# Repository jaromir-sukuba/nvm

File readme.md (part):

***Please note this nanovoltmeter design was superseded by a new and better design, which will go public in [this Github repository](https://github.com/jaromir-sukuba/nvm2). Soon(TM)***

## What is in this repository?
Here is the complete set of design files, manufacturing data, source files, test results and other resources that I used in the process of building a nanovoltmeter. This process was not a coincidence, but a response to the nanovoltmeter challenge by TiN on [his website](https://xdevs.com/article/nvm_comp/)

## What is a nanovoltmeter and what is it good for?
Well, a nanovoltmeter is a voltmeter that has the sensitivity, noise and stability to resolve voltages down to the nanovolt. While many multimeters do have quite sensitive low voltage ranges, the resolution (least significant digit) is usually in the order of hundreds of nanovolts - and value of this last digit is often diminished by the noise and nonlinearity of the meter. So, for proper low signal measurements, having a higher sensitivity is mandatory.
Measurement of such low voltages is useful for many applications, for example resolving small voltage differences in various differential and bridge circuits and the measurement of very small resistances - with an appropriate current source.
Commercial nanovoltmeters do exist, like the Keithley model 2182A or Keysight 34420A, but with a hefty price tag, so a DIY design definitely has its place.

## xDevs challenge
While I have been tinkering with DIY test and measurement tools for a while now, I never had an impulse to discover the nanovolt world. Such a trigger happened on September 2nd, 2021, when TiN from xdevs site launched the [nanovolt challenge](https://xdevs.com/article/nvm_comp/). In nutshell, it called for the design of an open-source nanovoltmeter, with parameters comparable to commercial designs and a timeframe of 256 days. That is a non-trivial task, and in my case it was even more so, because I had not only never designed low signal circuits before, but had I never operated a nanovoltmeter. That is quite an unfavorable starting position and jumping into the deep end rather than dipping my toes into the problematics. To ease my mind, I waited a few days to see how others reacted on the [eevblog forum](https://www.eevblog.com/forum/metrology/nanovolt-design-challenge-build-and-show-your-own-nv-meter-in-256-days/?all). I can't say that it encouraged me.
On the other hand, I spent a few days researching online sources and studying the service manuals of proven test gear from reputable vendors. Too bad they stopped supplying us with schematics in early 90s of the last century; but even that material was very helpful in understanding both what the requirements are for such a meter, as well as the means to achieve it.

## NVM design, part 1 - design requirements
Armed with new knowledge I started dissecting the challenge requirements. 

> Have local onboard power regulation. Single common DC (+9 to +24 VDC) or 110/220VAC mains input jack is expected.

Okay, I think I can do this. On the other hand, any reasonable mains-powered voltmeter has to have an isolated PSU section which powers the input dividers/amplifiers and ADC, so that the measurement potential could be unrelated to the digital section with all the user and communication IO - which is needed to be earthed or somewhere close to that potential.
This one calls for either DC or AC power, but it could be combined by having a PSU operating from an appropriate DC voltage (12V sounds like a good starting point) and attach a small AC/DC SMPS to provide power from mains.

> Provide DC Voltage measurement ranges ±100 µV or below and include ±1V and ±10VDC range.

This one looks innocent, but having both 10V and 100uV input on the same jacks implies either switching input amplifiers, or inserting a voltage divider into the signal path, preferably through a relay. Some older nanovoltmeters (Keithley model 181) had two different inputs - one for higher ranges, another one with low TEMF connector for sensitive ranges.

> Have at least two user-accessible input channels for signal to be measured.

Oh my, another relay. Relays are good, but may introduce offset errors into signals due to thermal voltages (TEMF, short for Thermal Electromotive Force) generated on the contacts, when the relay heats up from coil power. The voltages may be around a few microvolts down to nanovolts, definitely something to consider in this design. TEMF is the main enemy of the nanovoltmeter and this acronym will be used in following text a few more times.

> Have low-thermal connection interface to minimize thermal EMF parasitic errors.

TEMF again, I told you so.   
  
> Provide at least 5½-digit resolution for each reading.

Sounds reasonable. I've done long-scale ADC projects like [voltmeter](https://www.eevblog.com/forum/metrology/diy-6-5-digit-voltmeter/) and [voltohmmeter](https://www.eevblog.com/forum/metrology/diy-6-digit-handheld-volohmmeter/msg2978912/#msg2978912) so perhaps I could recycle something and also bring something new to the table. I think commercial sigma-delta A-to-D converters would do the job too, but a DIY ADC definitely has more to it.

> Ability to digitize input DC signal with resolution at least 10 nV and noise better than 30 nV peak to peak over at least 0.1-10 Hz bandwidth.

More numeric requirements, nice. 30nVp-p in 10Hz bandwidth is not a very relaxed requirement - older meters like Keithley model 181 would not cut it, current models so-so.

> Have autozero functionality to correct for static offsets.

That is a logical requirement. I will put in some more effort by introducing autocalibration.

> Have galvanic isolated analog front end, with isolation resistance to earth/chassis better than 10 GΩ.

That is what I proposed earlier, too. 

> Device should have ADC (any type) integrated.

This is likely to frame the project into standalone modus operandi.

> Have good long-term stability and use ovenized DC voltage reference (LM399, LTZ1000 or LTFLU with oven).

I wouldn't think of using anything worse than an LM399 (or ADR1399) anyway.

> Provide RJ45 Ethernet and/or IEEE-488 GPIB interface for communications with external world / external equipment.

Fair point. USB is simpler, though.

> 40W total input power budget (friendly to battery operation for sensitive experiments)

You wouldn't want your nanovoltmeter to consume more than 40W anyway. 40W is quite a bit of heat and it's not easy to dissipate it without introducing more TEMF errors.

> Device should be fully operational as standalone device (e.g. no debuggers or external equipment attached to make it work).

OK, fair.

After a bit of optimization, I came up with this block diagram.

It's basically done to fit the requirements above, with a few spicy parts I added for extra fun.
Input from either input connection is selected via an input multiplexor. There is also a third input, to be discussed later. This MUX passes the selected channel to a low noise amplifier (LNA) to be amplified and then routed via another MUX into the main amplifier. whose output is brought to the ADC. This ADC has a nominal 10V input range, so that the basic range with LNA is 10mV (10mV x 1000 = 10V). In order to have even more sensitive ranges, the main amplifier has option to switch to x1 (pass-through), x10 and x100 gain, combined into additional 1mV and 100uV ranges. When the LNA is bypassed, the input signal is brought directly to the main amplifier, allowing for 10V, 1V and 100mV ranges, seamlessly covering 100uV to 10V input range. That would make a nanovoltmeter already, but I added two more blocks - first is easy, a low-pass filter (also known as LPF) to cut down noise, especially on sensitive ranges. Another one is an auto-calibration block, which serves to decide the gain of both amplifiers. Ideally, the meter needs only to know its onboard 7V reference voltage and can derive lower ranges automatically without calibration/adjustment and keep it precise after resistors in dividers and amplifier drift due to age or temperature.
The entire upper portion of the circuit is held behind an isolation barrier in order to keep the input terminals separated from the power supply potential - either external DC or mains voltage. The bottom section consists mainly of the PSU and digital circuitry, including user IO and communication channels, like Ethernet and USB. For the added fun factor I also included GPIB as a low priority subproject.

## NVM design, part 2 - divide and conquer

Designing such an instrument, especially on a DIY base, is a lot of pingponging between mechanical and eletrical design. I could imagine how large the thing would be (say, an A4 page size as a footprint) and I knew I had to cram everything inside. Choosing a larger enclosure would give me much more freedom and other benefits (like easier dissipation of device heat, helping fight TEMF), but would be impractically large. Finding an appropriate enclosure wasn't easy - at first I thought of using G756 I used before in my [DIY SMU](https://github.com/jaromir-sukuba/J-SMU), but I preferred metal enclosures here - because of shielding from electrical interference, and with a steel enclosure even a bit of shielding from magnetic interference. Metal also helps with heat dissipation. Finally I settled on the 1EP802825 from Modushop.
That was the right time to take a look at the electrical domain. The Earthy and floating parts (separated by an isolation barrier) have to be physically separated in sub-enclosures (that calls for two PCBs minimum) and in order to have easier debugging and modification of the circuit, I decided to separate the floating part into two PCBs. One would hold FPGA control, the reference and ADC, while another one would consist of both amplifiers and ACAL circuits. Since the enclosure is 80mm tall, there is no problem stacking at least two PCBs on top of each other, via pin headers and metric spacers.
So, two PCBs for the floating part, one for the earthy part. The backside connectors have to be mounted somehow - here I added another PCB. The front panel pushbuttons also needed a PCB for mechanical reasons, that resulted in a total count of 5 PCBs. I named the PCBs with human names and gave them functionality:

**Bart** - I felt like this one will be tricky and there will be problems. Contains LNA, main amplifier, ACAL dividers and MUXes.  
**Homer** - largest PCB, contains FPGA, ADC, references. Closely related to Bart.  
**Lisa** - communication board, back panel PCB  
**Meggie** - simplest PCB, just to hold buttons  
**Marge** - contains PSU to feed all other PCBs, plus digital circuits.  

With the electronics roughly separated into basic blocks, I returned to mechanical design. By the time I finished first sketches of the schematics files, I received the enclosure, so I could start with more practical details. It's much easier to visualize potential problems having the real enclosure in hand compared to studying 3D files (if any, right). For circuit separation I opted for two sheet metal sub-enclosures.
. The smaller portion on right holding analog circuitry, the left portion holding earthy circuits - it's somehow shorter, to make room for a backpanel PCB.
I designed a bunch of holes into the enclosures to allow mounting PCBs via metric spacers, and now having physical constraints, I jumped back to PCB design.

## NVM design, part 3 - selected details of circuit operation
In this section I'll discuss a few selected design choices of this instrument.
#### LNA (Bart board)
I went through a few design iterations of the LNA and it took me roughly half of the development time. I tried DC-coupled JFET amplifiers, AC coupled JFET amplifiers in chopper configuration for DC operation as well as paralleling opamps. The parallel configuration brought me the least amount of headache and despite the insane amount of components used, it is not that expensive after all. As best in class, IF3602 JFETs are both expensive and suffer by huge parameter spread, making them quite an expensive solution. There are cheaper JFETs around, but their noise parameters mean more paralleled pieces - with problems they bring, for example binning and matching. More transistors or fewer low noise types also bring more gate capacitance, requiring more circuit support to diminish its influence. Enclosing the amplifier into chopper configuration brings more issues to solve - for example I had to deal with input current and temperature gradients increasing voltage offset. It's very likely that all those problems are solvable with more time and effort and would make an LNA with lower noise and drift than what I have in the current NVM, but at some point I decided to go a different way and built the LNA out of massively parallel off-the-shelf opamp amplifier. Integrated autozero/chopper opamps do have much better temperature stability and input current, so after a bit of searching and comparing I opted for MCP6V51 from Microchip, as the one with very good price/performance ratio. Typical input noise voltage is specified at 210nV in 10Hz bandwidth and I confirmed this experimentally by building a 35 piece opamp board first. 

The noise parameters were in good agreement with the datasheet values, that gave me confidence to go this way. As calculated, I need at least 50 MCP6V51s to get under 30nV p-p criteria, so I opted for 100 pieces, in 10x10 matrix, as per the schematic below

Each of the first stage gain blocks (with 10 amplifiers in parallel noninverting configuration) is brought to a second stage summing amplifier, and all 10 of the second stage amplifiers are summed into a third, and final, amplifier, with an overall gain of 1000.
The last stage summing amplifier is also used to inject a voltage to null the offset voltage of LNA. The Bart board has a DAC and its amplifiers (U119 and U120) for this reason. The DAC's second channel is designed to compensate for input current - by injecting a current of opposite sign into the LNA input. I measured the uncompensated current to be around 2nA and in my current hardware the injection resistor isn't fitted on the board. By using this feature, I expect a current well below 100pA.
The LNA injects ground current into the ground net of the circuit, and the current is dependent on input voltage (and therefore output voltage, too). Ground current may cause unwanted voltage shifts between ground potentials of the circuit, especially at high gains. To counteract this ground current, amplifier with U121 is set up to source current of opposite polarity into the ground, into areas where the LNA resides.
The Bart board is 4-layer, with internal layers being ground nets, for both electrical and thermal reasons.

#### ADC (Homer board)
The ADC is of the integrating, charge balancing type with residual integrator voltage reading. SN74LV4053 is used for integrator current steering, the integrator is of the classic two opamp composite type. The FPGA does multiple jobs here, apart from orchestrating actions around the ADC, it also provides an interface between isolated serial link and multiple digital outputs used to switch relays, multiplexer and analog filter and does startup timing for smooth PSU startup.
I measured INL of ADC against a Solartron 7081 as reference. A 0-10V voltage sweep was provided by a DIY precision voltage source (LTZ1000A reference, AD5791B DAC). Measured INL graph:

The INL of this magnitude may not be obviously needed for this application, but I wanted to employ ACAL functionality, where voltage transfer between ranges expects good INL of the ADC, so I was after good linearity and spent some time honing it.

#### PSU (Marge board)
My first idea for the PSU was to use two back-to-back 50Hz transformers. One would provide a few volts (providing first isolation barrier and ground reference) and the second would step it up to the level appropriate for +-16V and 5V DC outputs. Later I expended this idea by using an audio frequency amplifier circuit to feed the second transformer and omitting the first transformer. Using an AF amplifier (fed by an appropriate oscillator) to drive the transformer has a few advantages - the whole circuit could be powered from a single DC voltage and the oscillation frequency can be adjusted to find a good compromise between leakage and efficiency. Using classic linear amplifiers would bring way too much thermal dissipation into the enclosure, so I opted for the cheap and plentiful TPS3116 D-class amplifier. The oscillator signal - either from a local single opamp multivibrator or amplified signal provided by the MCU - is shaped by a series of lowpass filters, so that the amplifier is fed by a low harmonic content signal. Transformer secondary is brought to a fairly standard set of regulators - LM317/337 and 7805.
I measured ground leakage from the isolated PSU section and its efficiency as function of driving frequency.

As per expectations, a lower frequency also brings lower leakage current, but going too low causes efficiency to plummet at some point. I opted for 48Hz, where I measured leakage well below 200nA p-p. At this level, leakage measurement is very sensitive to nearby electric fields and conducted interference. After enclosing the test setup in a shielded box, the measured leakage fell to 40nA p-p, indicating the previous measurement was too pessimistic. I believe even the 40nA figure is pessimistic still and influenced by the shielding setup and the oscilloscope I used. For proper test results I'd need a larger shielded cage and a battery powered oscilloscope, but I didn't want to go that far.
The PSU design brought interesting detail to the game. In case of overload, TPS3116 will turn off the load drive. That sounds innocent, but may be problemtic in this case - because after powerup the reference is cold, so the heater takes a significant amount of current during powerup. To add insult to injury, all decoupling/bulk capacitors are discharged, even more increasing the powerup current spike. The spike causes TPS3116 to shut down for a moment, then it tries to restart the load, ending up in the same large spike, repeating again and again.
To mitigate this issue, two fixes were made:
 - PSU driving starts from higher frequency, slowly (over course of a few seconds) it descends to the final 48Hz value. Voltage on the isolated secondary ramps up much slower, allowing circuits to power up smoothly.  
 - Voltage reference heating current (large current spike when left untreated) and LNA power supply voltage is held off until 10 seconds after FPGA power gets stable, at which point heater current is enbled, and LNA power turns on two seconds later.

## Mechanical parts
While the enclosure is centered around the Modushop enclosure, a few more mechanical parts were needed.

#### Reference cover
This two-part 3D printed component prevents airflows around ADR1399 reference, decreasing its noise somehow.

#### Lisa board holder
This 3D printed component keeps Lisa board in its place on back panel.

#### LNA cover
This 3D printed component provides insulation of LNA board area from airflows.

The amount of influence on the readings was suprising to me. Here are two graphs of the shorted input measurement, one with cover, one without, the RMS noise voltage is nearly twofold for naked LNA.

#### Side PCB
The original modushop enclosure fitted the outer enclosure panel by screwing to side metal sheets by self tapping screws. I didn't like this, so I drilled the original holes for self-tappers into 3,5mm diameter and mounted dedicated mechanical PCB with nothing but holes and copper plane to solder M3 nuts. This PCB keeps the internal chassis and outer shields in single piece. I think this part would be somehow better made out of >3mm thick aluminium of the same size, with drilled and tapped holes, but PCB seems to work fine for now.

#### Push button rod
This is three piece 3D printed component to extend main switch shaft to front panel.  
TODO pictures.

#### Front panel construction
Display cover is epoxied into the front panel cutout, display is bolted to Meggie board and this board is bolted the to font panel.
TODO picture of perspex cutout

#### Internal construction details

Complete internal construction without top cover

Dump of construction photographs is in imgur gallery [here](https://imgur.com/a/fnK1Evj)

## NVM usage
#### Local interface

13 keys are provided for instrument operation, plus 2-line by 20 characters vacuum fluorescent display.
After startup the meter enters default (measurement) mode, with settings read from EEPROM. Typical display layout:

The first line displays measured voltage and range in obvious way.  
Second line in this example indicates following states:  
CH1 - selected channel 1. Could be either 1 or 2.  
Z0 - zero function (see below) is not active on this range. Could be either 0 or 1.  
10NPLC - ADC integration time in powerline cycle multiplies. Could be either 1, 2, 5, 10 or 20.  
ETH1 - Ethernet is connected and IP address provided via DHCP. Could be either 0 or 1.  

Buttons functions:  
**INPUT** - by clicking this button, the instrument toggles between Input 1 and Input 2 on the 4-pin LEMO connector.  
**ZERO** - this function enables zeroing measured value (by subtracting constant voltage offset measured at the instant of enabling the function). Each range has its offset value and is independent of other ranges. Zeroing for given range is disabled by second button press.  
**FILT** - pressing this button displays analog filter, digital filter and NPLC settings. Each hit of the button moves focus to next setting (value is changed by pressing UP/DOWN controls), third hit returns to default measurement display.  
**ACAL** - pressing this button starts ACAL procedure and saves the calibration constants into EEPROM memory.  
**TRIG** - not used in this firmware revision.  
**STORE** - not used in this firmware revision.  
**RECALL** - not used in this firmware revision.  
**MENU** - enables menu. Moving across menu items is done by pressing UP and DOWN keys. Enter enables editing the item value - editing is performed using UP and DOWN keys. Escaping from the menu is possible via ESC button, saving and escaping via MENU button.  
**AUTO** - not used in this firmware revision.  
**ENTER** - apart from function in menu function, pressing ENTER in default mode displays IP address of the instrument (if attached to ethernet). Pressing ENTER again returns back to default state.  
**UP/DOWN** - in menu or filter editing it serves function described above, in default mode it selects higher or lower measurement range.  

#### Remote interface
Instrument could be controlled remotely via ethernet interface, by issuing SCPI-compatible commands.  
\*IDN? - returns instrument identification  
\*RST - resets instrument  
\*CLS - clear status  
SYSTem:ERRor[:NEXT] - lists system error  
SYSTem:ERRor:COUNt? - return amount of system errors  
SYSTem:VERSion? - returns instrument version string  
MEASure:VOLTage? - returns value of measured voltage  
CALibration:VREF - single float parameter, sets value of 7V reference voltage (the only input for ACAL procedure)  
CALibration:VREF? - returns value of 7V reference voltage  
CALibration:UNLock - single integer parameter, locks (0) or unlocks (1) access to calibration EEPROM  
CALibration:SAVe - if access to calibration EEPROM is unlocked, this command saves actual calibration into EEPROM  
CALibration:ACAL - starts ACAL procedure  
SENSe:CHANnel - single integer parameter, sets channel 1 or 2  
SENSe:CHANnel? - returns actual channel number  
SENSe:RANGe - single integer parameter, sets range 1 (100uV) to 6 (10V)  
SENSe:RANGe? - returns actual range number  
SENSe:DFILter - single integer parameter, sets digital filter to 1, 2, 4, 8, 16, 32 or 64 samples  
SENSe:DFILter? - returns digital filter setting  
SENSe:AFILter - single integer parameter, sets analog filter off (0) or on (1)  
SENSe:AFILter? - returns analog filter setting  
SENSe:DIGits - single integer parameter, sets nubmer of displayed digits - 3 to 6  
SENSe:DIGits? - returns nubmer of displayed digits  
SENSe:NPLC - single integer parameter, sets ADC integration period in NPLC cycles to 1NPLC (0), or 2NPLC (1), or 5NPLC (2), or 10NPLC (3), or 20NPLC (4)  
SENSe:NPLC? - returns ADC integration period  
SENSe:AZero - single integer parameter, sets ADC autozero off (0) or on (1)  
SENSe:AZero? - return ADC autozero setting  
SYSTem:BEEPer - single integer parameter, sets beeper off (0) or on (1)  
SYSTem:BEEPer? - return beeper state  

NVM is fully calibrated by ACAL feature. For this it needs to have its reference voltage setup in calibration memory before running ACAL function. The value is accessible only through remote interface and its CALibration:VREF command. If the reference value in calibration memory is outside 6,95-7,3V range, default value 7,05V is assumed. At the moment, individual range calibration isn't supported, but probably will be in future firmware revisions.

## NVM project goals
In this section I'll discuss the performance of this instrument and project goals. 
#### Noise
The main criteria of this project was to achieve low noise at the lowest voltage range. In order to assess this, I logged 20 seconds of shorted input measurements at 100uV range, with no autozero, 2NPLC (integration time 40ms) and 10Hz analog filter on.

The noise is below 25nV p-p.
#### Stability
I recorded roughly 9 hours worth of data with shorted input, while logging ambient temperature too. Meter set to 10NPLC, autozero on, analog filter on. I separated the data into 64 seconds long chunks, averaged it and used as data points. I tried to control the room temperature to obtain some variation.

There is no clear temperature dependency. I read the data as sensitivity to temperature changes is perhaps more prominent than the tempco of the instrument.
#### Linearity
I measured the same INL of the NVM against Keithley 2010 as reference meter.

I believe it lies within acceptable margin for 6,5 digit meter.
#### Bandwidth and normal mode rejection
I measured ADC transfer function for sine input with 1Vp-p amplitude, stepped from 1Hz to 80Hz. Meter was set to 2NPLC, no autozero, analog filter on, 10V range.

Resulting bandwidth for -3dB is between 9 and 10Hz, normal mode rejection for 25, 50 and 75Hz is around -90dB
#### Stepping the input with various voltages from Keithley 260 voltage source
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
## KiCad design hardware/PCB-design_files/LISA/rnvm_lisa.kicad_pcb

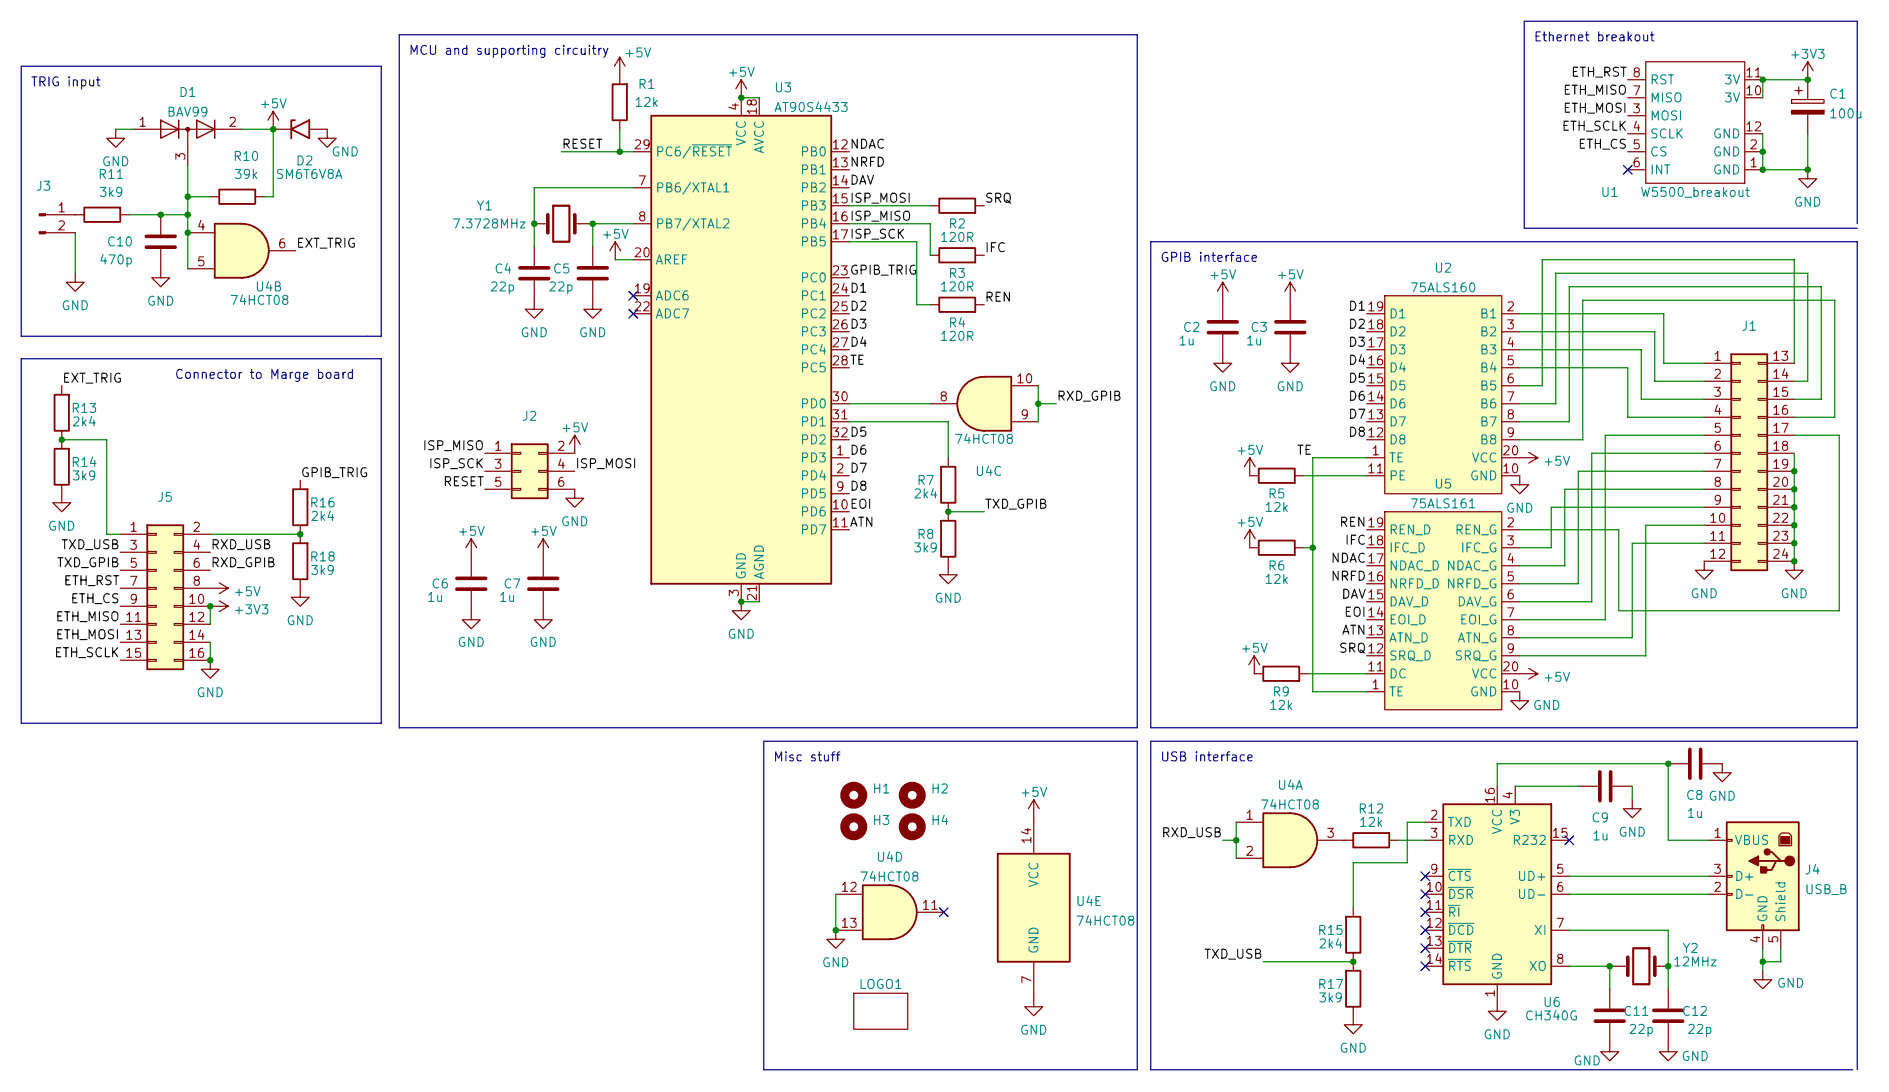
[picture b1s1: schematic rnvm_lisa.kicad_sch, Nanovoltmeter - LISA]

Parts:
C1: 100u; CP_EIA-7132-28_AVX-C_Pad2.72x3.50mm_HandSolder
C2, C3, C6, C7, C8, C9: 1u; C_0805_2012Metric_Pad1.18x1.45mm_HandSolder
C4, C5, C11, C12: 22p; C_0805_2012Metric_Pad1.18x1.45mm_HandSolder
C10: 470p; C_0805_2012Metric_Pad1.18x1.45mm_HandSolder
D1: BAV99; SOT-23
D2: SM6T6V8A; D_SMB
H1, H2, H3, H4: MountingHole; MountingHole_3.2mm_M3_DIN965_Pad
J1: Centronics 24, socket; CENTR_24P_F
J2: IDC_6pin; IDC-Header_2x03_P2.54mm_Vertical
J3: Conn_01x02_Male; Molex_KK-254_AE-6410-02A_1x02_P2.54mm_Vertical
J4: USB_B; USB_B_Lumberg_2411_02_Horizontal
J5: IDC_16; IDC-Header_2x08_P2.54mm_Vertical
LOGO1: PCB logo; logo_rpg7x9
R1, R5, R6, R9, R12: 12k; R_MiniMELF_MMA-0204
R2, R3, R4: 120R; R_MiniMELF_MMA-0204
R7, R13, R15, R16: 2k4; R_MiniMELF_MMA-0204
R8, R11, R14, R17, R18: 3k9; R_MiniMELF_MMA-0204
R10: 39k; R_MiniMELF_MMA-0204
U1: W5500_breakout; W5500_bo
U2: 75ALS160; SOIC-20W_7.5x12.8mm_P1.27mm
U3: AT90S4433; TQFP-32_7x7mm_P0.8mm
U4: 74HCT08; TSSOP-14_4.4x5mm_P0.65mm
U5: 75ALS161; SOIC-20W_7.5x12.8mm_P1.27mm
U6: CH340G; SOIC-16_3.9x9.9mm_P1.27mm
Y1: 7.3728MHz; Crystal_SMD_HC49-SD
Y2: 12MHz; Crystal_SMD_HC49-SD

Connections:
+3V3: C1.1, J5.10, J5.12, U1.10 (3V), U1.11 (3V)
+5V: C2.2, C3.2, C6.2, C7.2, D1.2 (A), D2.1 (A1), J2.2, J5.8, R1.2, R5.1, R6.1, R9.1, R10.2, U2.20 (VCC), U3.4 (VCC), U3.6 (VCC), U3.18 (AVCC), U3.20 (AREF), U4.14 (VCC), U5.20 (VCC)
/ATN: U3.11 (PD7), U5.13 (ATN_D)
/D1: U2.19 (D1), U3.24 (PC1)
/D2: U2.18 (D2), U3.25 (PC2)
/D3: U2.17 (D3), U3.26 (PC3)
/D4: U2.16 (D4), U3.27 (PC4)
/D5: U2.15 (D5), U3.32 (PD2)
/D6: U2.14 (D6), U3.1 (PD3)
/D7: U2.13 (D7), U3.2 (PD4)
/D8: U2.12 (D8), U3.9 (PD5)
/DAV: U3.14 (PB2), U5.15 (DAV_D)
/EOI: U3.10 (PD6), U5.14 (EOI_D)
/ETH_CS: J5.9, U1.5 (CS)
/ETH_MISO: J5.11, U1.7 (MISO)
/ETH_MOSI: J5.13, U1.3 (MOSI)
/ETH_RST: J5.7, U1.8 (RST)
/ETH_SCLK: J5.15, U1.4 (SCLK)
/EXT_TRIG: R13.2, U4.6
/GPIB_TRIG: R16.2, U3.23 (PC0)
/IFC: R3.2, U5.18 (IFC_D)
/ISP_MISO: J2.1, R3.1, U3.16 (PB4)
/ISP_MOSI: J2.4, R2.1, U3.15 (PB3)
/ISP_SCK: J2.3, R4.1, U3.17 (PB5)
/NDAC: U3.12 (PB0), U5.17 (NDAC_D)
/NRFD: U3.13 (PB1), U5.16 (NRFD_D)
/REN: R4.2, U5.19 (REN_D)
/RESET: J2.5, R1.1, U3.29 (PC6/~RESET)
/RXD_GPIB: J5.6, U4.9, U4.10
/RXD_USB: J5.4, U4.1, U4.2
/SRQ: R2.2, U5.12 (SRQ_D)
/TE: R6.2, U2.1 (TE), U3.28 (PC5), U5.1 (TE)
/TXD_GPIB: J5.5, R7.1, R8.2
/TXD_USB: J5.3, R15.1, R17.2
GND: C1.2, C2.1, C3.1, C4.2, C5.2, C6.1, C7.1, C8.2, C9.2, C10.2, C11.2, C12.2, D1.1 (K), D2.2 (A2), J1.12, J1.18, J1.19, J1.20, J1.21, J1.22, J1.23, J1.24, J2.6, J3.2, J4.4 (GND), J4.5 (Shield), J5.14, J5.16, R8.1, R14.1, R17.1, R18.1, U1.1 (GND), U1.2 (GND), U1.12 (GND), U2.10 (GND), U3.3 (GND), U3.5 (GND), U3.21 (AGND), U4.7 (GND), U4.12, U4.13, U5.10 (GND), U6.1 (GND)
unnamed: C4.1, U3.7 (PB6/XTAL1), Y1.1
unnamed: C5.1, U3.8 (PB7/XTAL2), Y1.2
unnamed: C8.1, J4.1 (VBUS), U6.16 (VCC)
unnamed: C9.1, U6.4 (V3)
unnamed: C10.1, D1.3 (K), R10.1, R11.2, U4.4, U4.5
unnamed: C11.1, U6.8 (XO), Y2.2
unnamed: C12.1, U6.7 (XI), Y2.1
unnamed: J1.1, U2.2 (B1)
unnamed: J1.2, U2.3 (B2)
unnamed: J1.3, U2.4 (B3)
unnamed: J1.4, U2.5 (B4)
unnamed: J1.5, U5.7 (EOI_G)
unnamed: J1.6, U5.6 (DAV_G)
unnamed: J1.7, U5.5 (NRFD_G)
unnamed: J1.8, U5.4 (NDAC_G)
unnamed: J1.9, U5.3 (IFC_G)
unnamed: J1.10, U5.9 (SRQ_G)
unnamed: J1.11, U5.8 (ATN_G)
unnamed: J1.13, U2.6 (B5)
unnamed: J1.14, U2.7 (B6)
unnamed: J1.15, U2.8 (B7)
unnamed: J1.16, U2.9 (B8)
unnamed: J1.17, U5.2 (REN_G)
unnamed: J3.1, R11.1
unnamed: J4.2 (D-), U6.6 (UD-)
unnamed: J4.3 (D+), U6.5 (UD+)
unnamed: J5.1, R13.1, R14.2
unnamed: J5.2, R16.1, R18.2
unnamed: R5.2, U2.11 (PE)
unnamed: R7.2, U3.31 (PD1)
unnamed: R9.2, U5.11 (DC)
unnamed: R12.1, U4.3
unnamed: R12.2, U6.3 (RXD)
unnamed: R15.2, U6.2 (TXD)
unnamed: U3.30 (PD0), U4.8

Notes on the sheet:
MCU and supporting circuitry
Connector to Marge board
Misc stuff
USB interface
TRIG input
Ethernet breakout
GPIB interface

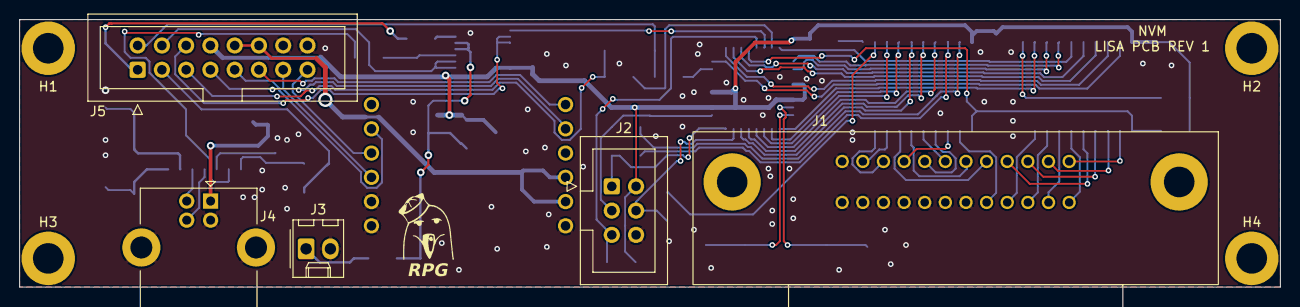
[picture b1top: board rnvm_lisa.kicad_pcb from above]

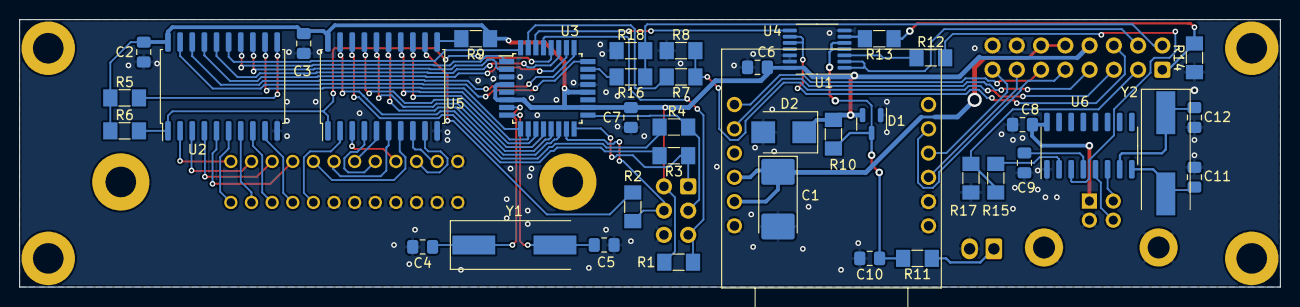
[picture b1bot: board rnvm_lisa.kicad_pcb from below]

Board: 2 copper layers, 132.0 x 28.0 mm, 50 parts (40 on the bottom side), 70 nets.

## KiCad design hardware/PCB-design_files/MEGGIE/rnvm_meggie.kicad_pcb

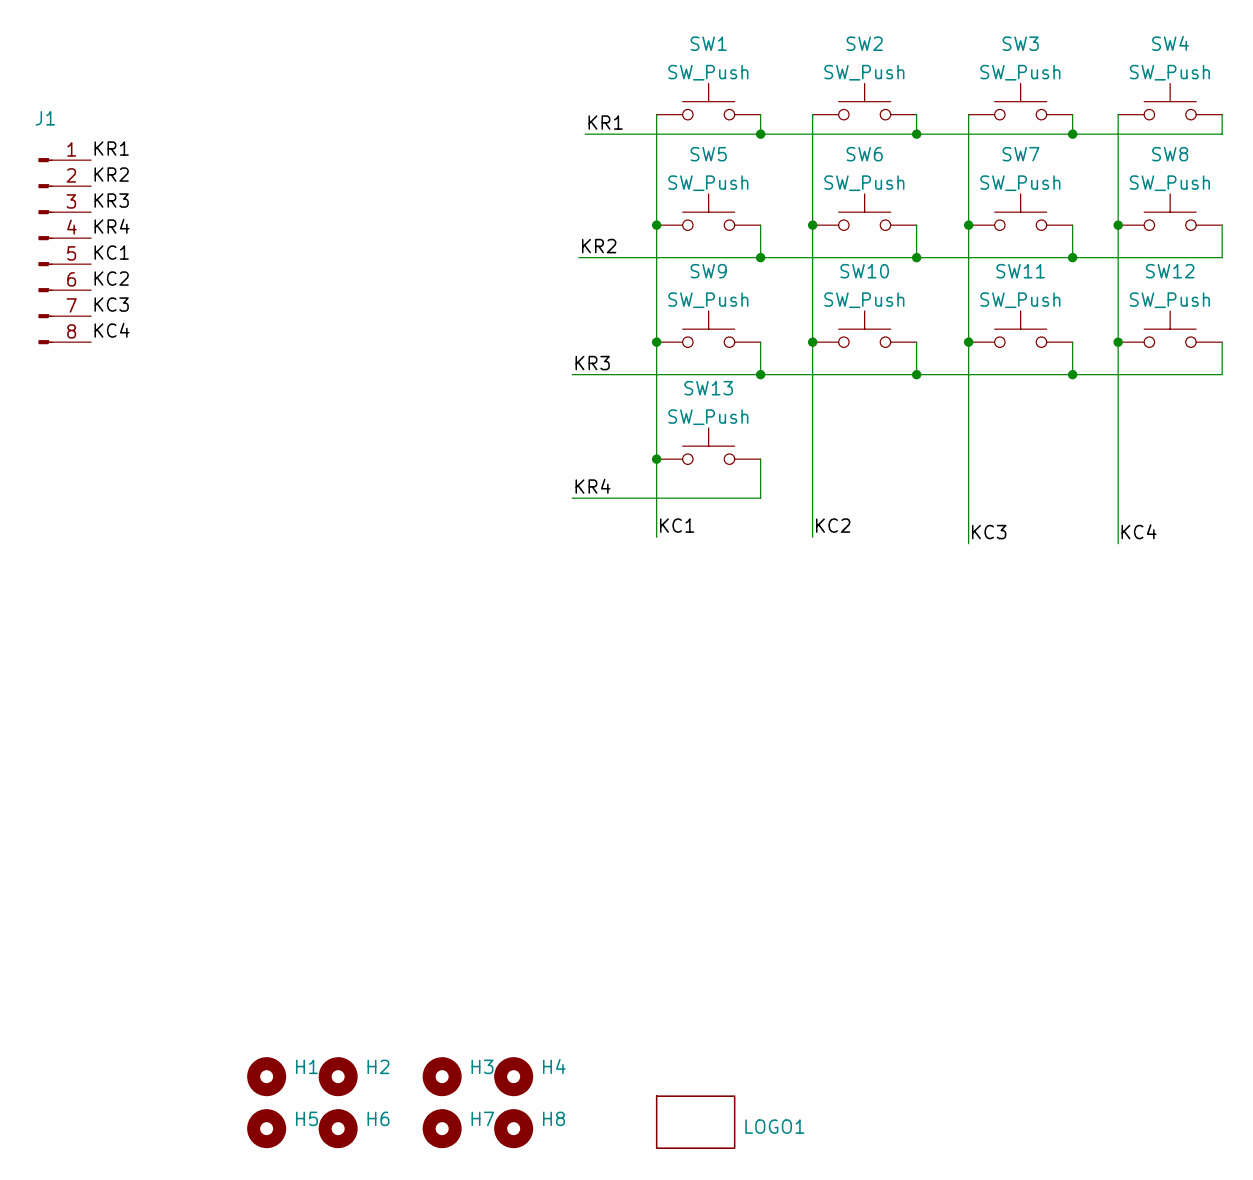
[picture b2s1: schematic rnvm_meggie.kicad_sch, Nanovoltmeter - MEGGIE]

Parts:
H1, H2, H5, H6: MountingHole; MountingHole_2.5mm_Pad
H3, H4, H7, H8: MountingHole; MountingHole_3.2mm_M3_DIN965_Pad
J1: Conn_01x08_Male; Molex_KK-254_AE-6410-08A_1x08_P2.54mm_Vertical
LOGO1: logo_generic; logo_rpg7x9
SW1, SW2, SW3, SW4, SW5, SW6, SW7, SW8, SW9, SW10, SW11, SW12, SW13: SW_Push; MQ_6450

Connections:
/KC1: J1.5, SW1.1, SW5.1, SW9.1, SW13.1
/KC2: J1.6, SW2.1, SW6.1, SW10.1
/KC3: J1.7, SW3.1, SW7.1, SW11.1
/KC4: J1.8, SW4.1, SW8.1, SW12.1
/KR1: J1.1, SW1.2, SW2.2, SW3.2, SW4.2
/KR2: J1.2, SW5.2, SW6.2, SW7.2, SW8.2
/KR3: J1.3, SW9.2, SW10.2, SW11.2, SW12.2
/KR4: J1.4, SW13.2

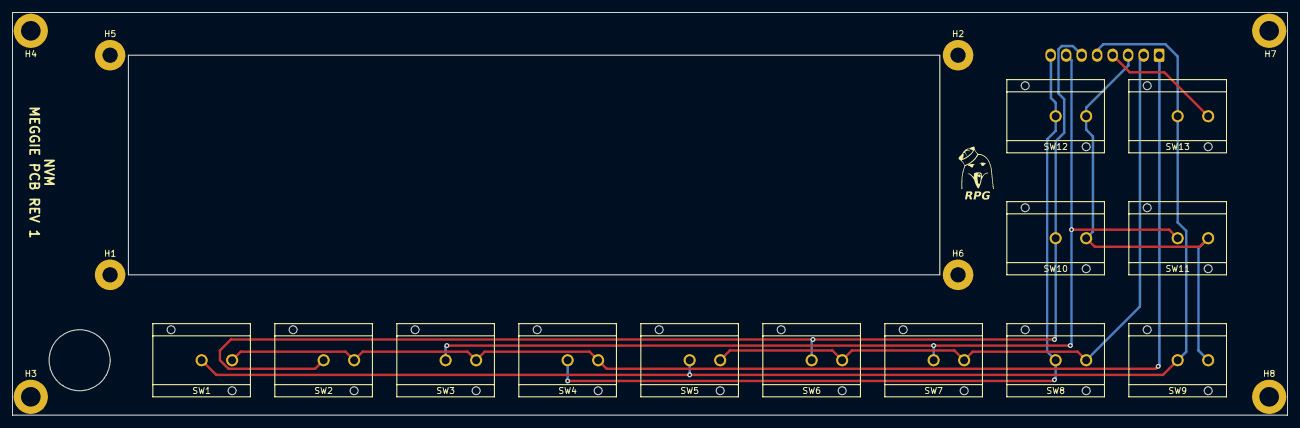
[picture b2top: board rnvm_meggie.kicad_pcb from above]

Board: 2 copper layers, 209.0 x 66.0 mm, 23 parts (1 on the bottom side), 8 nets.

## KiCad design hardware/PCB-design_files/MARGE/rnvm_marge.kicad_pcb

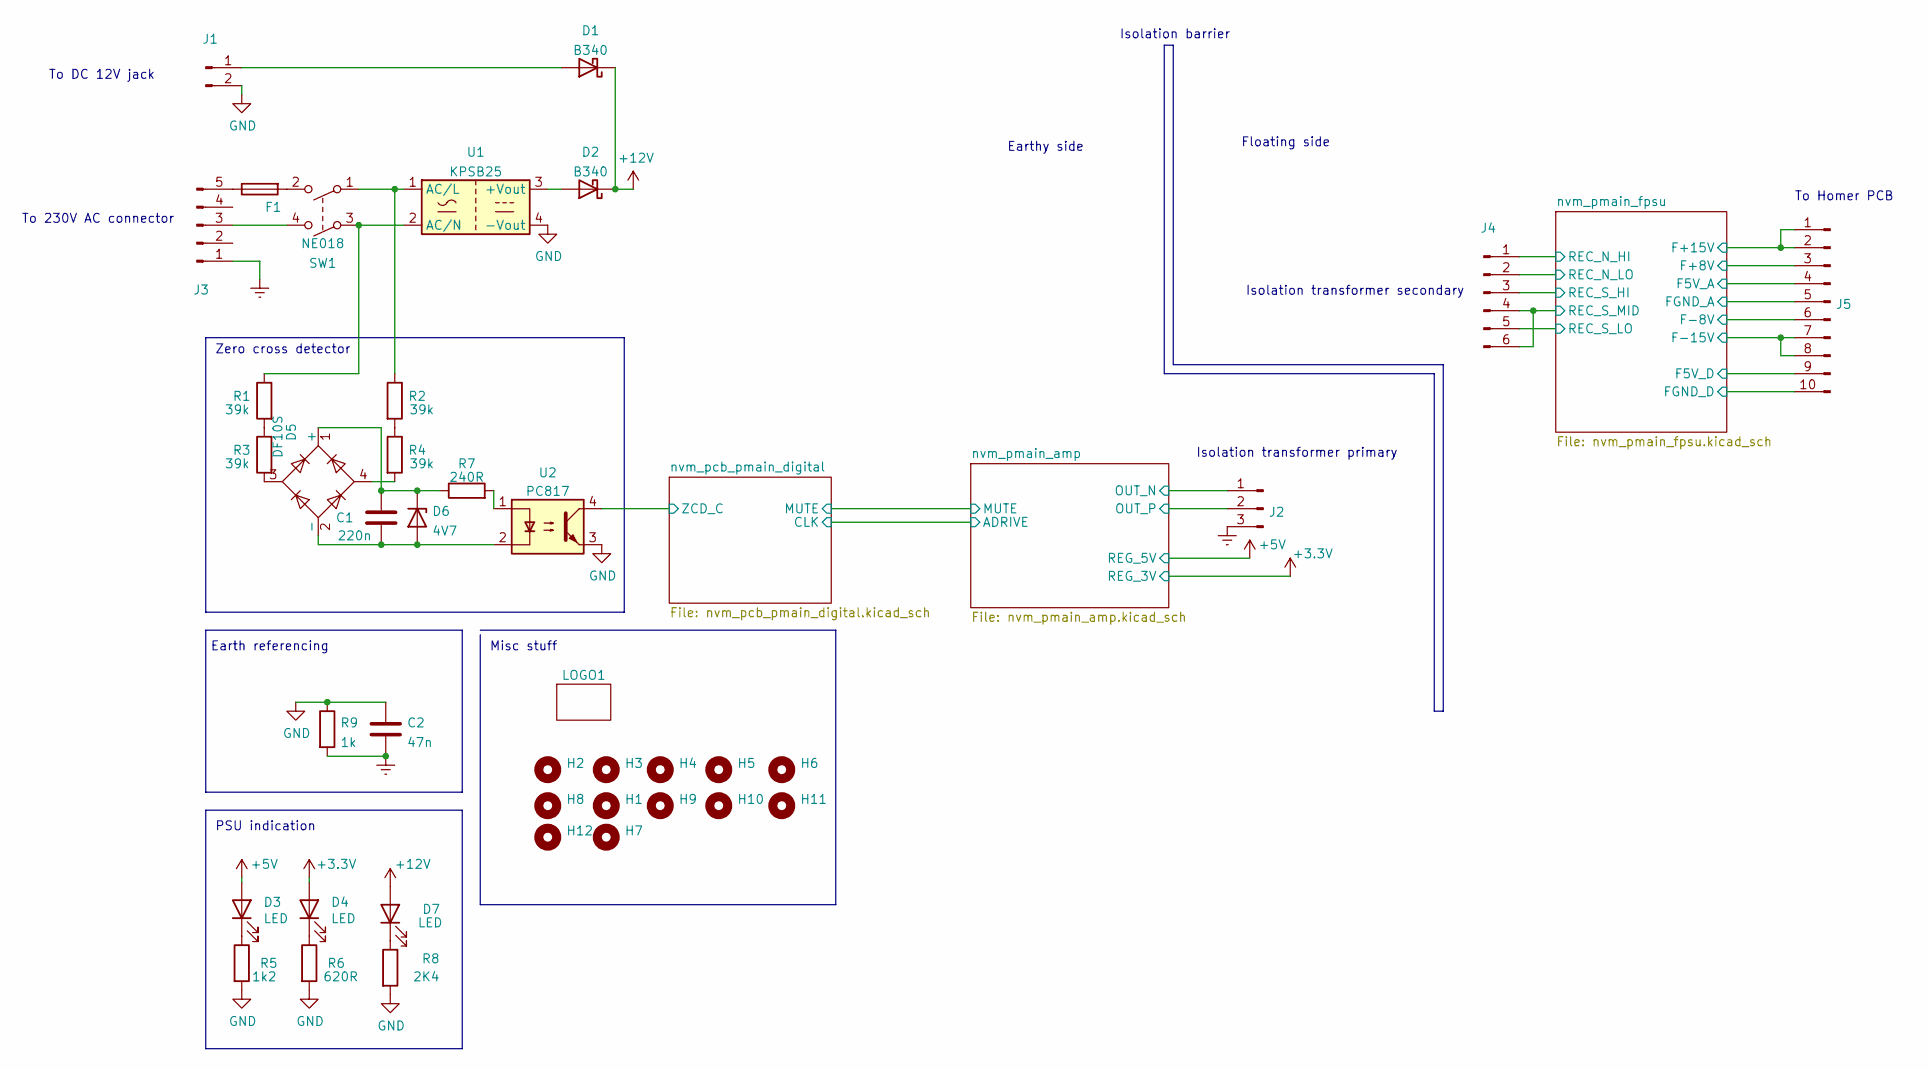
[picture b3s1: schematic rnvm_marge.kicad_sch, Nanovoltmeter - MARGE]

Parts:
C1: 220n; C_0805_2012Metric_Pad1.18x1.45mm_HandSolder
C2: 47n; C_Rect_L18.0mm_W6.0mm_P15.00mm_FKS3_FKP3
D1, D2: B340; D_SMC
D3, D4, D7: LED; LED_0805_2012Metric_Pad1.15x1.40mm_HandSolder
D5: DF10S; Diode_Bridge_Diotec_SO-DIL-Slim
D6: 4V7; D_MiniMELF
F1: Fuse; Fuseholder_Cylinder-5x20mm_Schurter_0031_8201_Horizontal_Op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
H1, H7, H12: MountingHole; MountingHole_3.2mm_M3_DIN965_Pad
H2, H3, H4, H5, H6, H8, H9, H10, H11: MountingHole; MountingHole_3.2mm_M3
J1: Conn_01x02_Male; Molex_KK-396_A-41791-0002_1x02_P3.96mm_Vertical
J2: Conn_01x03_Male; Molex_KK-396_A-41791-0003_1x03_P3.96mm_Vertical
J3: Conn_01x05_Male; Molex_KK-396_A-41791-0005_1x05_P3.96mm_Vertical
J4: Conn_01x06_Male; Molex_KK-396_A-41791-0006_1x06_P3.96mm_Vertical
J5: Conn_01x10_Male; Molex_KK-254_AE-6410-10A_1x10_P2.54mm_Vertical
LOGO1: logo_generic; logo_rpg7x9
R1, R2, R3, R4: 39k; R_MiniMELF_MMA-0204
R5: 1k2; R_MiniMELF_MMA-0204
R6: 620R; R_MiniMELF_MMA-0204
R7: 240R; R_MiniMELF_MMA-0204
R8: 2K4; R_MiniMELF_MMA-0204
R9: 1k; R_Axial_DIN0411_L9.9mm_D3.6mm_P12.70mm_Horizontal
SW1: NE018; NE18-2P
U1: KPSB25
U2: PC817; SMDIP-4_W9.53mm

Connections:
+3V3: D4.2 (A); also elsewhere on the board
+5V: D3.2 (A); also elsewhere on the board
+12V: D1.1 (K), D2.1 (K), D7.2 (A); also elsewhere on the board
/nvm_pcb_pmain_digital/ZCD_C: U2.4; also elsewhere on the board
/nvm_pmain_amp/OUT_N: J2.1; also elsewhere on the board
/nvm_pmain_amp/OUT_P: J2.2; also elsewhere on the board
/nvm_pmain_fpsu/F5V_A: J5.4; also elsewhere on the board
/nvm_pmain_fpsu/F5V_D: J5.9; also elsewhere on the board
/nvm_pmain_fpsu/F+8V: J5.3; also elsewhere on the board
/nvm_pmain_fpsu/F+15V: J5.1, J5.2; also elsewhere on the board
/nvm_pmain_fpsu/F-8V: J5.6; also elsewhere on the board
/nvm_pmain_fpsu/F-15V: J5.7, J5.8; also elsewhere on the board
/nvm_pmain_fpsu/FGND_A: J5.5; also elsewhere on the board
/nvm_pmain_fpsu/FGND_D: J5.10; also elsewhere on the board
/nvm_pmain_fpsu/REC_N_HI: J4.1; also elsewhere on the board
/nvm_pmain_fpsu/REC_N_LO: J4.2; also elsewhere on the board
/nvm_pmain_fpsu/REC_S_HI: J4.3; also elsewhere on the board
/nvm_pmain_fpsu/REC_S_LO: J4.5; also elsewhere on the board
/nvm_pmain_fpsu/REC_S_MID: J4.4, J4.6; also elsewhere on the board
Earth: C2.2, J2.3, J3.1, R9.2
GND: C2.1, J1.2, R5.2, R6.2, R8.2, R9.1, U1.4 (-Vout), U2.3; also elsewhere on the board
unnamed: C1.1, D5.2 (-), D6.2 (A), U2.2
unnamed: C1.2, D5.1 (+), D6.1 (K), R7.1
unnamed: D1.2 (A), J1.1
unnamed: D2.2 (A), U1.3 (+Vout)
unnamed: D3.1 (K), R5.1
unnamed: D4.1 (K), R6.1
unnamed: D5.3, R3.2
unnamed: D5.4, R4.2
unnamed: D7.1 (K), R8.1
unnamed: F1.1, J3.5
unnamed: F1.2, SW1.2
unnamed: J3.3, SW1.4
unnamed: R1.1, SW1.3, U1.2 (AC/N)
unnamed: R1.2, R3.1
unnamed: R2.1, SW1.1, U1.1 (AC/L)
unnamed: R2.2, R4.1
unnamed: R7.2, U2.1

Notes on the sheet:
To Homer PCB
Earth referencing
To DC 12V jack
Zero cross detector
PSU indication
Misc stuff
Floating side
Isolation barrier
Earthy side
To 230V AC connector
Isolation transformer secondary
Isolation transformer primary

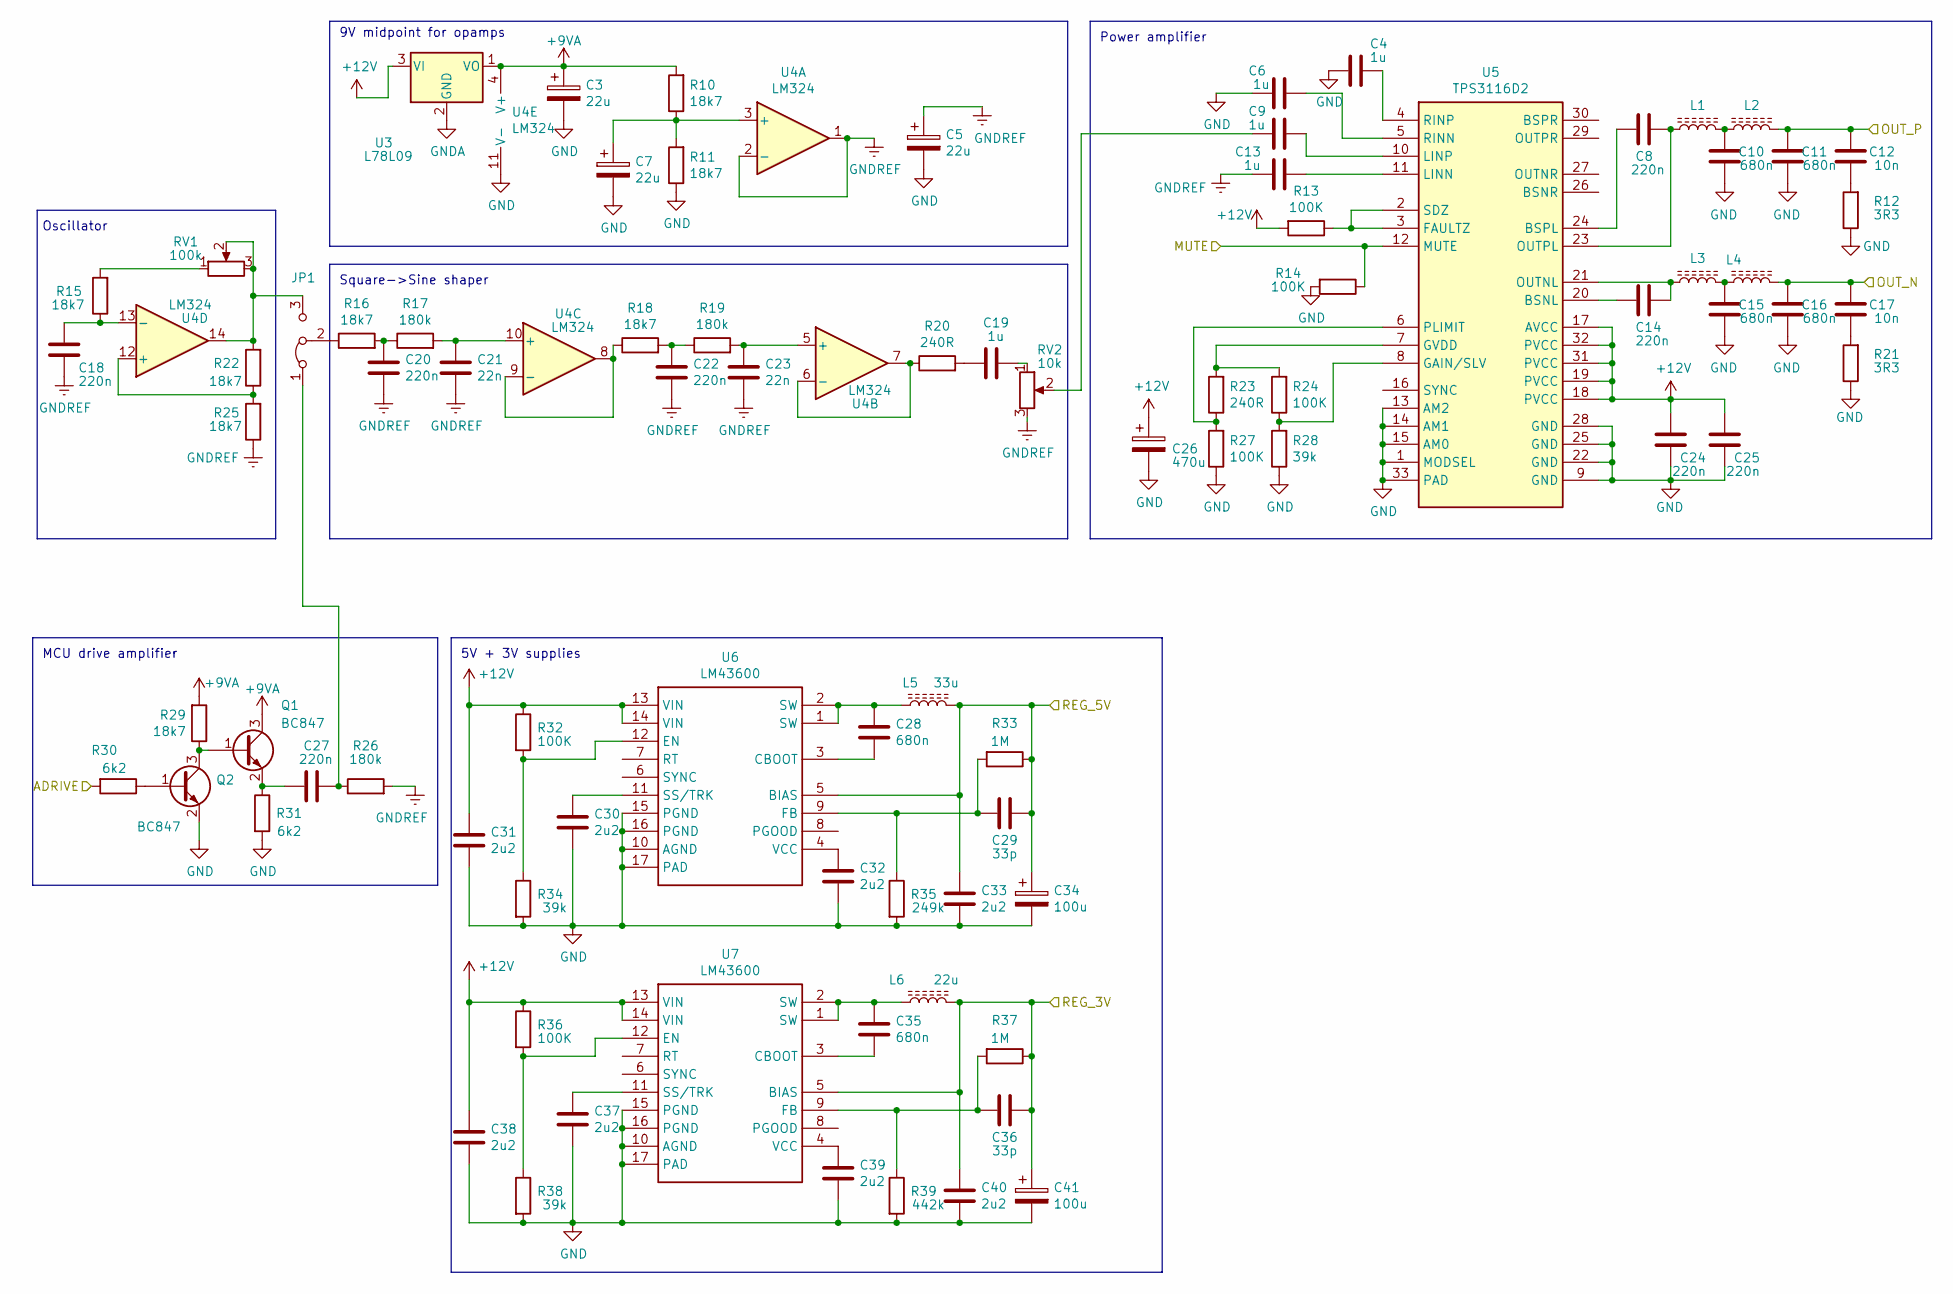
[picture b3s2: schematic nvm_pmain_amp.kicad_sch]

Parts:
C3, C5, C7: 22u; CP_Radial_D5.0mm_P2.50mm
C4, C6, C9, C13, C19: 1u; C_Rect_L7.0mm_W3.5mm_P5.00mm
C8, C14, C24, C25, C27: 220n; C_0805_2012Metric_Pad1.18x1.45mm_HandSolder
C10, C11, C15, C16, C28, C35: 680n; C_0805_2012Metric_Pad1.18x1.45mm_HandSolder
C12, C17: 10n; C_0805_2012Metric_Pad1.18x1.45mm_HandSolder
C18, C20, C22: 220n; C_Rect_L7.0mm_W3.5mm_P5.00mm
C21, C23: 22n; C_Rect_L7.0mm_W3.5mm_P5.00mm
C26: 470u; CP_Radial_D8.0mm_P3.50mm
C29, C36: 33p; C_0805_2012Metric_Pad1.18x1.45mm_HandSolder
C30, C31, C32, C33, C37, C38, C39, C40: 2u2; C_0805_2012Metric_Pad1.18x1.45mm_HandSolder
C34, C41: 100u; CP_EIA-7343-31_Kemet-D_Pad2.25x2.55mm_HandSolder
JP1: Jumper_3_Bridged12; PinHeader_1x03_P2.54mm_Vertical
L1, L2, L3, L4: 10u; L_10.4x10.4_H4.8
L5: 33u; L_Coilcraft_LPS5030
L6: 22u; L_Coilcraft_LPS5030
Q1, Q2: BC847; SOT-23
R10, R11, R15, R16, R18, R22, R25, R29: 18k7; R_MiniMELF_MMA-0204
R12, R21: 3R3; R_MiniMELF_MMA-0204
R13, R14, R24, R27, R32, R36: 100K; R_MiniMELF_MMA-0204
R17, R19, R26: 180k; R_MiniMELF_MMA-0204
R20, R23: 240R; R_MiniMELF_MMA-0204
R28, R34, R38: 39k; R_MiniMELF_MMA-0204
R30, R31: 6k2; R_MiniMELF_MMA-0204
R33, R37: 1M; R_MiniMELF_MMA-0204
R35: 249k; R_MiniMELF_MMA-0204
R39: 442k; R_MiniMELF_MMA-0204
RV1: 100k; Potentiometer_Bourns_3296W_Vertical
RV2: 10k; Potentiometer_Bourns_3296W_Vertical
U3: L78L09; TO-92_Wide
U4: LM324; SO-14_3.9x8.65mm_P1.27mm
U5: TPS3116D2; HTSSOP-32-1EP_6.1x11mm_P0.65mm_EP5.2x11mm_Mask4.11x4.36mm
U6, U7: LM43600; HTSSOP-16-1EP_4.4x5mm_P0.65mm_EP3.4x5mm_Mask2.46x2.31mm

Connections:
+3V3: C36.1, C40.1, C41.1, L6.2, R37.1, U7.5 (BIAS); also elsewhere on the board
+5V: C29.1, C33.1, C34.1, L5.2, R33.1, U6.5 (BIAS); also elsewhere on the board
+9VA: C3.1, Q1.3 (C), R10.2, R29.2, U3.1 (VO), U4.4 (V+)
+12V: C24.2, C25.2, C26.1, C31.1, C38.1, R13.2, R32.1, R36.1, U3.3 (VI), U5.17 (AVCC), U5.18 (PVCC), U5.19 (PVCC), U5.31 (PVCC), U5.32 (PVCC), U6.13 (VIN), U6.14 (VIN), U7.13 (VIN), U7.14 (VIN); also elsewhere on the board
/nvm_pcb_pmain_digital/MUTE: R14.1, U5.12 (MUTE); also elsewhere on the board
/nvm_pcb_pmain_digital/S_DRIV: R30.2; also elsewhere on the board
/nvm_pmain_amp/OUT_N: C16.2, C17.2, L4.2; also elsewhere on the board
/nvm_pmain_amp/OUT_P: C11.2, C12.2, L2.2; also elsewhere on the board
GND: C3.2, C4.2, C5.2, C6.2, C7.2, C10.1, C11.1, C15.1, C16.1, C24.1, C25.1, C26.2, C30.2, C31.2, C32.2, C33.2, C34.2, C37.2, C38.2, C39.2, C40.2, C41.2, Q2.2 (E), R11.1, R12.1, R14.2, R21.1, R27.1, R28.1, R31.2, R34.2, R35.2, R38.2, R39.2, U4.11 (V-), U5.1 (MODSEL), U5.9 (GND), U5.13 (AM2), U5.14 (AM1), U5.15 (AM0), U5.22 (GND), U5.25 (GND), U5.28 (GND), U5.33 (PAD), U6.10 (AGND), U6.15 (PGND), U6.16 (PGND), U6.17 (PAD), U7.10 (AGND), U7.15 (PGND), U7.16 (PGND), U7.17 (PAD); also elsewhere on the board
GNDA: U3.2 (GND)
GNDREF: C5.1, C13.2, C18.2, C20.2, C21.2, C22.2, C23.2, R25.1, R26.2, RV2.3, U4.1, U4.2 (-)
unnamed: C4.1, U5.4 (RINP)
unnamed: C6.1, U5.5 (RINN)
unnamed: C7.1, R10.1, R11.2, U4.3 (+)
unnamed: C8.1, L1.1, U5.23 (OUTPL)
unnamed: C8.2, U5.24 (BSPL)
unnamed: C9.1, U5.10 (LINP)
unnamed: C9.2, RV2.2
unnamed: C10.2, L1.2, L2.1
unnamed: C12.1, R12.2
unnamed: C13.1, U5.11 (LINN)
unnamed: C14.1, L3.1, U5.21 (OUTNL)
unnamed: C14.2, U5.20 (BSNL)
unnamed: C15.2, L3.2, L4.1
unnamed: C17.1, R21.2
unnamed: C18.1, R15.1, U4.13 (-)
unnamed: C19.1, RV2.1
unnamed: C19.2, R20.2
unnamed: C20.1, R16.2, R17.1
unnamed: C21.1, R17.2, U4.10 (+)
unnamed: C22.1, R18.2, R19.1
unnamed: C23.1, R19.2, U4.5 (+)
unnamed: C27.1, JP1.1 (A), R26.1
unnamed: C27.2, Q1.2 (E), R31.1
unnamed: C28.1, L5.1, U6.1 (SW), U6.2 (SW)
unnamed: C28.2, U6.3 (CBOOT)
unnamed: C29.2, R33.2, R35.1, U6.9 (FB)
unnamed: C30.1, U6.11 (SS/TRK)
unnamed: C32.1, U6.4 (VCC)
unnamed: C35.1, L6.1, U7.1 (SW), U7.2 (SW)
unnamed: C35.2, U7.3 (CBOOT)
unnamed: C36.2, R37.2, R39.1, U7.9 (FB)
unnamed: C37.1, U7.11 (SS/TRK)
unnamed: C39.1, U7.4 (VCC)
unnamed: JP1.2 (C), R16.1
unnamed: JP1.3 (B), R22.2, RV1.2, RV1.3, U4.14
unnamed: Q1.1 (B), Q2.3 (C), R29.1
unnamed: Q2.1 (B), R30.1
unnamed: R13.1, U5.2 (SDZ), U5.3 (FAULTZ)
unnamed: R15.2, RV1.1
unnamed: R18.1, U4.8, U4.9 (-)
unnamed: R20.1, U4.6 (-), U4.7
unnamed: R22.1, R25.2, U4.12 (+)
unnamed: R23.1, R27.2, U5.6 (PLIMIT)
unnamed: R23.2, R24.2, U5.7 (GVDD)
unnamed: R24.1, R28.2, U5.8 (GAIN/SLV)
unnamed: R32.2, R34.1, U6.12 (EN)
unnamed: R36.2, R38.1, U7.12 (EN)

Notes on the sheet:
9V midpoint for opamps
Oscillator
Square->Sine shaper
Power amplifier
5V + 3V supplies
MCU drive amplifier
